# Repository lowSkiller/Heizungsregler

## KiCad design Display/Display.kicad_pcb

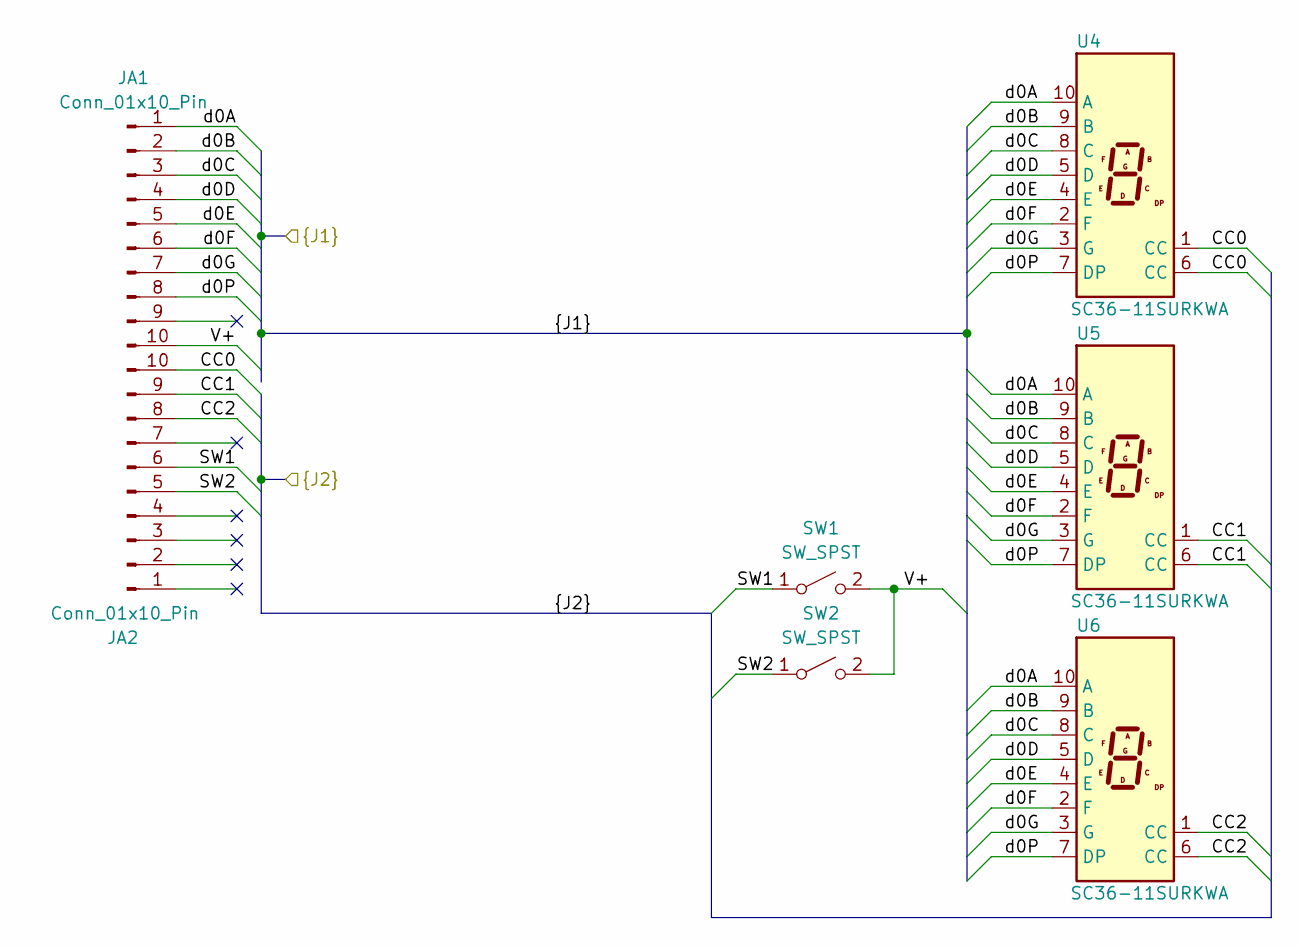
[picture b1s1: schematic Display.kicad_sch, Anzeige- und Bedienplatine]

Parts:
JA1, JA2: Conn_01x10_Pin; PinHeader_1x10_P2.54mm_Vertical
SW1, SW2: SW_SPST; SW_Tactile_Pollin_6x6mm_12V_50mA_P5,21mm
U4, U5, U6: SC36-11SURKWA; Sx36-1xxxxx

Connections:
/CC0: JA2.10, U4.1 (CC), U4.6 (CC)
/CC1: JA2.9, U5.1 (CC), U5.6 (CC)
/CC2: JA2.8, U6.1 (CC), U6.6 (CC)
/SW1: JA2.6, SW1.1 (A)
/SW2: JA2.5, SW2.1 (A)
/V+: JA1.10, SW1.2 (B), SW2.2 (B)
/d0A: JA1.1, U4.10 (A), U5.10 (A), U6.10 (A)
/d0B: JA1.2, U4.9 (B), U5.9 (B), U6.9 (B)
/d0C: JA1.3, U4.8 (C), U5.8 (C), U6.8 (C)
/d0D: JA1.4, U4.5 (D), U5.5 (D), U6.5 (D)
/d0E: JA1.5, U4.4 (E), U5.4 (E), U6.4 (E)
/d0F: JA1.6, U4.2 (F), U5.2 (F), U6.2 (F)
/d0G: JA1.7, U4.3 (G), U5.3 (G), U6.3 (G)
/d0P: JA1.8, U4.7 (DP), U5.7 (DP), U6.7 (DP)

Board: 2 copper layers, 7 parts (0 on the bottom side), 14 nets, no tracks yet.

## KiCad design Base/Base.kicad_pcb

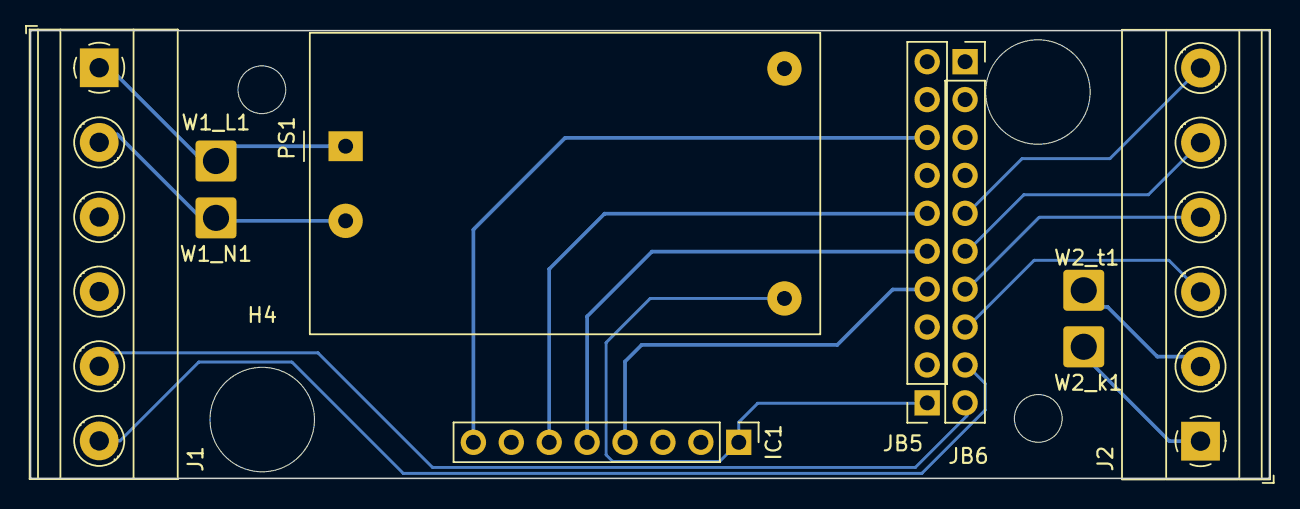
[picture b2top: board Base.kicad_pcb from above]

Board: 2 copper layers, 83.0 x 30.0 mm, 14 parts (0 on the bottom side), 16 nets.

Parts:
H1, H2: MountingHole; MountingHole_3.2mm_M3_DIN965
H3, H4: CaseMountingHole; MountingHole_7mm
IC1: Conn_01x08; PinHeader_1x08_P2.54mm_Vertical
J1, J2: Screw_Terminal_01x06; TerminalBlock_Phoenix_MKDS-1,5-6_1x06_P5.00mm_Horizontal
JB5, JB6: Conn_01x10_Socket; PinSocket_1x10_P2.54mm_Vertical
PS1: HLK-PM01; Converter_ACDC_HiLink_HLK-PMxx
W1_L1, W1_N1, W2_k1, W2_t1: Wire; SolderWire-1sqmm_1x01_D1.4mm_OD2.7mm

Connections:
/RST: IC1.8, JB5.8
/SDI: IC1.6, JB5.6
/SDO: IC1.5, JB5.5
/SLK: IC1.4, JB5.4
/SW+: J1.5, JB6.10
/SW-: J1.6, JB6.9
/V+: IC1.1, JB5.1, PS1.4 (+Vout)
/V-: IC1.2, IC1.7, JB5.2, PS1.3 (-Vout)
/tr+: J2.5, JB6.6
/tr-: J2.6, JB6.5
/tv+: J2.3, JB6.8
/tv-: J2.4, JB6.7
unnamed: J1.1, PS1.1 (AC/L), W1_L1.1
unnamed: J1.2, PS1.2 (AC/N), W1_N1.1
unnamed: J2.1, W2_k1.1
unnamed: J2.2, W2_t1.1

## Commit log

2024-03-04 Restored license GNU GENERAL PUBLIC LICENSE
